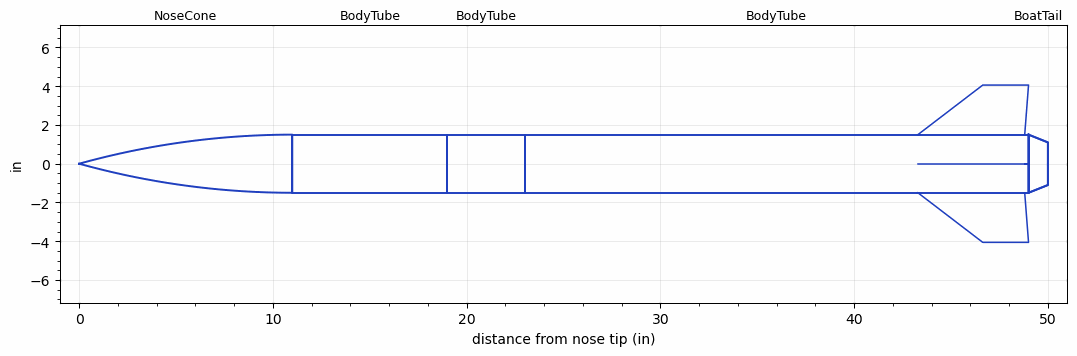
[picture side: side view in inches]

<RASAeroDocument>
 <FileVersion>2</FileVersion>
 <RocketDesign>
  <NoseCone>
   <Length>11</Length>
   <Diameter>3</Diameter>
   <Shape>Tangent Ogive</Shape>
   <Location>0</Location>
  </NoseCone>
  <BodyTube>
   <Length>8</Length>
   <Diameter>3</Diameter>
   <Location>11</Location>
  </BodyTube>
  <BodyTube>
   <Length>4</Length>
   <Diameter>3</Diameter>
   <Location>19</Location>
  </BodyTube>
  <BodyTube>
   <Length>26</Length>
   <Diameter>3</Diameter>
   <Location>23</Location>
   <BoattailLength>1</BoattailLength>
   <BoattailRearDiameter>2.2</BoattailRearDiameter>
   <Fin>
    <Count>4</Count>
    <Chord>5.511811</Chord>
    <Span>2.559055</Span>
    <SweepDistance>3.346457</SweepDistance>
    <TipChord>2.362205</TipChord>
    <Thickness>0.25</Thickness>
    <Location>5.708661</Location>
    <AirfoilSection>Square</AirfoilSection>
   </Fin>
  </BodyTube>
  <BoatTail>
   <Length>1</Length>
   <Diameter>3</Diameter>
   <RearDiameter>2.2</RearDiameter>
   <Location>49</Location>
  </BoatTail>
  <Surface>Smooth (Zero Roughness)</Surface>
  <ModifiedBarrowman>False</ModifiedBarrowman>
  <Turbulence>False</Turbulence>
  <UseBooster1>False</UseBooster1>
  <UseBooster2>False</UseBooster2>
 </RocketDesign>
 <LaunchSite>
  <Altitude>0</Altitude>
  <Pressure>0</Pressure>
  <RodAngle>0</RodAngle>
  <RodLength>4</RodLength>
  <Temperature>74</Temperature>
  <WindSpeed>0</WindSpeed>
 </LaunchSite>
 <Recovery>
  <Altitude1>1000</Altitude1>
  <Altitude2>1000</Altitude2>
  <DeviceType1>None</DeviceType1>
  <DeviceType2>None</DeviceType2>
  <Event1>False</Event1>
  <Event2>False</Event2>
  <Size1>1</Size1>
  <Size2>1</Size2>
  <EventType1>None</EventType1>
  <EventType2>None</EventType2>
  <CD1>1.33</CD1>
  <CD2>1.33</CD2>
 </Recovery>
 <SimulationList>
  <Simulation>
   <SustainerEngine>H238T  (AT)</SustainerEngine>
   <SustainerLaunchWt>2.9</SustainerLaunchWt>
   <SustainerNozzleDiameter>1</SustainerNozzleDiameter>
   <SustainerCG>32</SustainerCG>
   <SustainerIgnitionDelay>0</SustainerIgnitionDelay>
   <Booster1SeparationDelay>0</Booster1SeparationDelay>
   <Booster1IgnitionDelay>0</Booster1IgnitionDelay>
   <IncludeBooster1>False</IncludeBooster1>
   <Booster2Delay>0</Booster2Delay>
   <IncludeBooster2>False</IncludeBooster2>
   <TimetoApogee>8.880108</TimetoApogee>
   <MaxAltitude>1459.591</MaxAltitude>
   <MaxVelocity>397.3884</MaxVelocity>
   <OptimumWt>1.6675</OptimumWt>
   <OptimumMaxAlt>1.6675</OptimumMaxAlt>
  </Simulation>
 </SimulationList>
</RASAeroDocument>
